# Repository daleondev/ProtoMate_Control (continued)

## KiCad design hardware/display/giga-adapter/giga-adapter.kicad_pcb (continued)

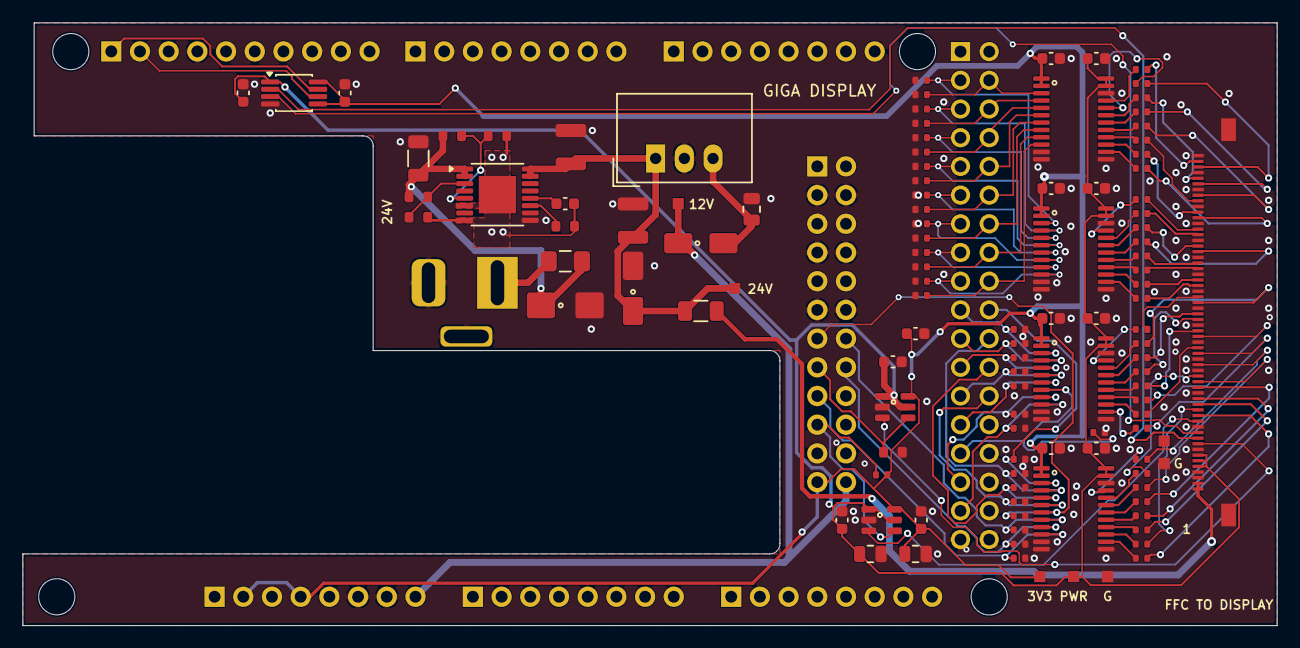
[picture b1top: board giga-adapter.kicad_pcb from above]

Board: 4 copper layers, 111.0 x 53.3 mm, 127 parts (0 on the bottom side), 118 nets.

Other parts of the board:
H1, H2, H3, H4: MountingHole_3.2mm_M3

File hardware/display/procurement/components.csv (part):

Board,Revision,Designators,Installed quantity,Purchase quantity,Circuit value,PCB package,Assembly,Original BOM MPN,Purchase manufacturer,Purchase MPN,Mouser part number,Availability evidence,Indexed stock,Index age,Lookup date,Source URL,Notes
display-adapter,G,J1,1,1,DF23C-50DP-0.5V(92),DF23C-50DP-0.5V,SMT,DF23C-50DP-0.5V(92),Hirose,DF23C-50DP-0.5V(92),798-DF23C50DP05V92,stock-indexed,1575,2 weeks ago,2026-10-22,https://www.mouser.com/en/ProductDetail/Hirose-Connector/DF2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,Exact 50-pin mating plug; fit on display PCB underside.
display-adapter,G,J2,1,1,505110-6091,Molex_505110-6091_1x60_P0.50mm,SMT,505110-6091,Molex,505110-6091,538-505110-6091,stock-indexed,11530,last week,2026-10-22,https://eu.mouser.com/en/ProductDetail/Molex/505110-6091?qs=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,Two bottom-contact sockets per pair; match Molex 15018-0563 Type-A ear-tab cable.
display-adapter,G,U1,1,1,TSR 2-2433 / 3.3V 2A,Converter_DCDC_TRACO_TSR2-xxxx_THT,HAND,TSR 2-2433,TRACO Power,TSR 2-2433,495-TSR2-2433,stock-indexed,6134,3 weeks ago,2026-10-22,https://eu.mouser.com/en/ProductDetail/TRACO-Power/TSR-2-243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,3.3 V / 2 A; through-hole SIP module.
display-adapter,G,"C9, C11",2,2,10u / 50V X7R,C_1210_3225Metric,SMT,GRM32ER71H106KA12L,TAIYO YUDEN,MCJCU32MLB7106KPPDTJ,963-U32MLB7106KPPDTJ,stock-indexed,1535,2 months ago,2026-10-22,https://my.mouser.com/en/ProductDetail/TAIYO-YUDEN/MCJCU32ML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,"Replacement: 10 uF +/-10%, 50 V, X7R, 1210, soft termination; 2.5 +/-0.3 mm height. Original unavailable/region-restricted."
display-adapter,G,C10,1,1,100n / 50V X7R,C_0603_1608Metric,SMT,GRM188R71H104KA93D,KEMET,C0603C104K5RACTU,80-C0603C104K5R,stock-indexed,3941024,last week,2026-10-22,https://cz.mouser.com/en/ProductDetail/KEMET/C0603C104K5RACT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,"Replacement for obsolete original: 100 nF +/-10%, 50 V, X7R, 0603."
display-adapter,G,"C1, C2, C3, C4, C12, C13, C14",7,7,47u / 10V X5R,C_1210_3225Metric,SMT,GRM32ER61A476KE20L,TAIYO YUDEN,MBASL32MSB5476KPNA01,963-BASL32MSB5476KP,stock-indexed,1608,2 weeks ago,2026-10-23,https://lv.mouser.com/en/ProductDetail/TAIYO-YUDEN/MBASL32MS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,"Approved purchasing replacement: 47 uF +/-10%, 10 V, X5R, 1210; 2.5 +/-0.2 mm height. Manufacturer typical DC-bias curve gives approximately 42 uF at 3.3 V and 36 uF at 5 V, not guaranteed minima. Retain supply/ramp/load-step qualification. No footprint change."
display-adapter,G,"C5, C6",2,2,10u / 10V X5R,C_0805_2012Metric,SMT,GRM21BR61A106KE19L,KEMET,C0805C106K8PACTU,80-C0805C106K8P,stock-indexed,235800,last week,2026-10-22,https://eu.mouser.com/en/ProductDetail/KEMET/C0805C106K8PACT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,"Replacement for obsolete original: 10 uF +/-10%, 10 V, X5R, 0805; 1.25 +/-0.15 mm height."
display-adapter,G,"C7, C8, C16, C18, C17",5,5,100n / 50V X7R,C_0603_1608Metric,SMT,GRM188R71C104KA01D,KEMET,C0603C104K5RACTU,80-C0603C104K5R,stock-indexed,3941024,last week,2026-10-22,https://cz.mouser.com/en/ProductDetail/KEMET/C0603C104K5RACT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,"Replacement for EOL original: 100 nF +/-10%, X7R, 0603; voltage rating increased from 16 V to 50 V. Consolidated with display C10."
display-adapter,G,"R2, R3, R4, R5, R8",5,5,47k,R_0402_1005Metric,SMT,RC0402FR-0747KL,YAGEO,RC0402FR-0747KL,603-RC0402FR-0747KL,stock-indexed,986351,last month,2026-10-22,https://eu.mouser.com/en/ProductDetail/YAGEO/RC0402FR-0747KL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,"47 kohm, 1%, 0402."
display-adapter,G,"R6, R7",2,2,4k7,R_0402_1005Metric,SMT,RC0402FR-074K7L,YAGEO,RC0402FR-074K7L,603-RC0402FR-074K7L,stock-indexed,5902658,last week,2026-10-22,https://www.mouser.com/en/ProductDetail/YAGEO/RC0402FR-074K7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,"4.7 kohm, 1%, 0402."
display-adapter,G,U2,1,1,TSR 1-2450 / 5V 1A,Converter_DCDC_TRACO_TSR-1_THT_Trimmed,HAND,TSR 1-2450,TRACO Power,TSR 1-2450,495-TSR-1-2450,stock-indexed,13356,3 weeks ago,2026-10-22,https://eu.mouser.com/en/ProductDetail/TRACO-Power/TSR-1-245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,5 V / 1 A; through-hole SIP module.
display-adapter,G,U3,1,1,TPS7A9101DSKT,WSON-10-1EP_2.5x2.5mm_P0.5mm_EP1.2x2mm,SMT,TPS7A9101DSKR,Texas Instruments,TPS7A9101DSKT,595-TPS7A9101DSKT,stock-indexed,105,3 weeks ago,2026-10-22,https://eu.mouser.com/en/ProductDetail/Texas-Instruments/TPS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,Packaging-only replacement: same DSK-10 chip/pinout; small-reel suffix T instead of R. Exposed pad must be soldered.
display-adapter,G,C15,1,1,47n / 50V X7R,C_0603_1608Metric,SMT,GRM188R71C473KA01D,TDK,C1608X7R1H473K080AA,810-C1608X7R1H473K,stock-indexed,69961,3 weeks ago,2026-10-23,https://www.mouser.com/en/ProductDetail/TDK/C1608X7R1H473K08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,"Approved purchasing replacement: 47 nF +/-10%, 50 V, X7R, 0603; same nominal specification as the unavailable KEMET selection, voltage rating exceeds released BOM 16 V. No footprint change."
display-adapter,G,R9,1,1,31.2k / 0.1%,R_0603_1608Metric,SMT,RT0603BRD0731K2L,Vishay,TNPW060331K2BEEN,71-TNPW060331K2BEEN,stock-indexed,280,last month,2026-10-22,https://www.mouser.tw/en/ProductDetail/Vishay/TNPW060331K2BE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,"Replacement: 31.2 kohm, 0.1%, 25 ppm/K, 0603. Preserve precision LDO ratio; original backordered."
display-adapter,G,R10,1,1,10k / 0.1%,R_0603_1608Metric,SMT,RT0603BRD0710KL,YAGEO,RT0603BRD0710KL,603-RT0603BRD0710KL,stock-indexed,69151,last week,2026-10-22,https://eu.mouser.com/en/ProductDetail/YAGEO/RT0603BRD0710KL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,"10 kohm, 0.1%, 25 ppm/K, 0603. Do not confuse with ordinary 1% 10 kohm."
display-adapter,G,"R11, R12, R13, R14, R15",5,5,10k / 1%,R_0603_1608Metric,SMT,RC0603FR-0710KL,YAGEO,RC0603FR-0710KL,603-RC0603FR-0710KL,stock-indexed,1640807,last week,2026-10-22,https://www.mouser.com/en/ProductDetail/YAGEO/RC0603FR-0710K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,"10 kohm, 1%, 0603."
display-adapter,G,"U4, U6",2,2,TPS3808EG33DBVR,SOT-23-6_UpperPin1,SMT,TPS3808G33DBVR,Texas Instruments,TPS3808EG33DBVR,595-TPS3808EG33DBVR,user-confirmed-orderable,4336,last week,2026-10-23,https://www.mouser.de/ProductDetail/Texas-Instruments/TPS380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,"TPS3808E functional replacement, not a packaging-only substitution: same DBV SOT-23-6 pinout, 3.07 V nominal threshold and active-low open-drain reset. Existing 100 kohm CT pull-ups retain 300 ms nominal delay (180-420 ms). 3.3 V operation is within the 1.7-6 V range; 10 kohm RESET pull-up is compatible. Lower typical quiescent current (0.6 uA). Datasheet undervoltage detect delay is 30 us typical / 50 us maximum at 5% overdrive; retain first-board brownout qualification. User confirmed regional purchase availability for the required two parts on 2026-10-23; stock quantity remains indexed, not live verified. No circuit or footprint change."
display-adapter,G,"R16, R17",2,2,100k,R_0402_1005Metric,SMT,RC0402FR-07100KL,YAGEO,RC0402FR-07100KL,603-RC0402FR-07100KL,stock-indexed,6394487,last month,2026-10-22,https://www.mouser.com/en/ProductDetail/YAGEO/RC0402FR-07100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,"100 kohm, 1%, 0402."
display-adapter,G,U5,1,1,SN74LVC08APW,TSSOP-14_4.4x5mm_P0.65mm,SMT,SN74LVC08APWR,Texas Instruments,SN74LVC08APW,595-SN74LVC08APW,stock-indexed,252,last month,2026-10-22,https://www.mouser.com/en/ProductDetail/Texas-Instruments/SN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,"Packaging-only replacement: same TSSOP-14 PW chip, supplied in tube; original reel variant backordered."
giga-adapter,F,J1,1,1,505110-6091,Molex_505110-6091_1x60_P0.50mm,SMT,505110-6091,Molex,505110-6091,538-505110-6091,stock-indexed,11530,last week,2026-10-22,https://eu.mouser.com/en/ProductDetail/Molex/505110-6091?qs=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,Two bottom-contact sockets per pair; match Molex 15018-0563 Type-A ear-tab cable.
giga-adapter,F,"U1, U2, U3, U4",4,4,SN74AXC8T245PWR,TSSOP-24_4.4x7.8mm_P0.65mm,SMT,SN74AXC8T245PWR,Texas Instruments,SN74AXC8T245PWR,595-SN74AXC8T245PWR,stock-indexed-conflicting,4862,last week,2026-10-22,https://gr.mouser.com/en/c/semiconductors/logic-ics/?mountin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,Latest indexed category page reports stock; older product page reports zero. Confirm four available at basket import. TSSOP-24; no AXCH/LVC substitution.
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
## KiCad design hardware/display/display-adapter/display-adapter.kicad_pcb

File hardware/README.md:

# ProtoMate hardware

Open **[ProtoMate.kicad_pro](ProtoMate.kicad_pro)** in KiCad 10. This is the single
hardware project: the complete system schematic and the linked perfboard layout
share the same project name and component identities.

```text
hardware/
├── ProtoMate.kicad_pro       Project settings and electrical checks
├── ProtoMate.kicad_sch       Root sheet: controller, power, sheet navigation
├── ProtoMate.kicad_pcb       47 × 65 hole perfboard placement and hand wiring
├── sheets/                  Motor interfaces, encoder, storage, headers, switches
├── libraries/               Project-local symbols, footprints and buck 3D model
├── sym-lib-table            Relative symbol-library registration
├── fp-lib-table             Relative footprint-library registration
├── assembly/                Build instructions, parts, hole/wire/harness tables
├── exports/                 Schematic/assembly PDFs and verification reports
└── tools/                   Repeatable checks and export command
```

## Schematic and layout relationship

The root schematic links six child sheets: M1/DM542T, M2/M3/TMC2209,
M1 encoder, storage, perfboard cable headers, and reference limit switches.
Global net names connect these sheets electrically. The connector sheet defines
J101–J107 and J113, and the reference-switch sheet defines J108–J111.
J104 is the ten-way DM542T screw terminal for control, ALM and 24 V power.
The M1 sheet defines pull-up R30; J101 carries ALM to the Nucleo. All connector pin numbers match the layout and
[harness table](assembly/Harness.csv).

All **49 perfboard footprints** have assigned library footprints and native
links to their schematic symbols. These comprise Q1–Q6, R1–R12, R20–R30,
C1–C6, U2/U3, J101–J111 and J113. R10–R12 remain on the layout and are marked DNP.

The **buck U1 and Adafruit A3/A4 modules mount directly at J103/J105/J106**.
These footprints represent their soldered mounting pins and full module
outlines. The module symbols remain excluded from separate PCB placement:
the barrel jack and four-way motor terminals remain on their modules.
J103 has four electrical contacts: 5 V output, output ground, VIN ground and
24 V input. J105/J106 each have ten JP4 control pins plus two JP1 power pins.
J104.9/10 provide the DM542T power connection and the two power-distribution
star joints. Dedicated underside supply/return branches feed each TMC module
through its local C1/C2 bulk capacitor connections. Motor winding cables
connect directly to the drivers. The Nucleo, DM542T, motors, switches and
storage modules remain external. The buck's 63 × 27 mm body follows the supplied
STEP model; its nominal mounting grid is 5.08 mm within each pair and 50.8 mm
between pairs. Its barrel jack receives 24 V at the left edge.

J113 uses eight contacts for six signals and two shared ground returns to the Nucleo: TX (PD5),
RX (PD6), M2 DIAG (PD4), M3 DIAG (PD3), M2 INDEX (PD0) and M3 INDEX (PD1). R29 is the shared UART's 1 kΩ TX
series resistor. J105/J106 pin 9 is UART, pin 7 is DIAG and pin 8 is INDEX.
Address straps are M2 MS1/MS2 = GND/GND and M3 = 3.3 V/GND. Both SPRD jumpers
stay open. Firmware configures current and 16 microsteps before enable; the
potentiometers do not set current in UART mode. See the
[UART wiring and firmware settings](../README.md#tmc2209-uart-configuration-and-diagnostics).

The `.kicad_pcb` is a map for a purchased individual-pad board: F.Cu represents
top jumpers, B.Cu represents solder-side wires, and vias represent wire passages.
Use the **65 × 47-hole board**, oriented as **47 columns × 65 rows**, A1–BM47,
at 2.54 mm pitch. The outer hole centres span **116.84 × 162.56 mm**; the
nominal outline is 119.38 × 165.10 mm with half-pitch margins. J104 and both TMC modules
sit along the top edge with their cable entries facing outward. J107 sits below
J104, keeping both motor-1 cables together. J101, J113, J102 and J108 form a
left-edge Nucleo connector bank with 9.1 mm gaps between bodies and pin 1 at
the bottom of every header. The encoder receiver and level converters occupy
the centre-left; the DM542T transistor stages occupy the right interior.
The buck sits at the bottom left, with the three switch cable headers at the
bottom right. Q1–Q3 have 30.48 mm between stages; Q4–Q6 have
15.24 mm between stages. Decoupling capacitors stay close to their ICs.
The barrel jack faces the left edge.
The wire schedule specifies underside routes and insulated top crossovers
through dedicated free holes. All wire ends are soldered underneath. J101's pin 1 is
at Z4; odd pins run up column 4 and even pins up column 3. The 11 designated
power connections all stay underneath and use 0.5 mm² insulated copper wire;
wire drawing width does not specify conductor size.
Use the [assembly instructions](assembly/README.md) to build it.

The STEP engine uses one 32-bit TIM2 with DMA: M1 = PA0/CN10.29,
M2 = PB10/CN10.32, M3 = PB11/CN10.34 (channels 1/3/4, all AF1).
DIR uses PE12/CN10.26, PE13/CN10.10, PE14/CN10.8; the shared active-low
enable is PE15/CN10.30. These signals use J101 pins 1/3/5/7/9/11/12. J101.4 carries M1 ALM,
J101.8 supplies 3.3 V, and pins 2/6/10 are STEP ground returns.
The harness table, Nucleo symbol and layout notes specify the cable destinations.
Keep PA0's SB75 ON and the user
button on PC13. TIM5 is the runtime clock; TIM7 provides an internal finite-move
completion check and uses no connector pin. PE9/PE11 (TIM1) and PC6/PC7
(TIM8) are reserved for possible additional encoders, with no cables fitted.

Set the onboard **STLINK-V3 MCO to HSE/5 (5 MHz)**. CubeMX uses that external
clock in bypass mode for a 480 MHz CPU, 240 MHz timer kernels and 10 MHz STEP
counter. This persistent ST-Link setting is configured separately from CubeMX;
follow the [clock setup procedure](../docs/stepper-hardware-test.md#clock-source-configuration)
when preparing a board.

The three reference-switch cables connect to J109 (M1), J110 (M2), and J111
(M3), each with pin 1 = REF and pin 2 = GND. J108 returns the signals to
PE7/CN10.20, PE8/CN10.18 and PE10/CN10.24 on pins 1/2/3; pin 4
connects their shared return to Nucleo GND/CN10.22. This is passive wiring using the
firmware's internal 3.3 V pull-ups. SW1–SW3 are shown released with COM–NC
closed: low when released, high when pressed or unplugged. Their schematic
contact names are functional identities, not an asserted Creality connector
pin order; verify the normally closed pair by continuity before making cables.

J104.7/8 connects DM542T ALM+/ALM−; J101.4 returns the signal
to PF2/CN9.17, sharing the motion harness ground. R30 pulls ALM+ to 3.3 V through 4.7 kΩ.
The default normally conducting alarm reads low when healthy and high on a
fault or open cable. See the
[alarm wiring and recovery behavior](../README.md#dm542t-alarm-input).

## Controller harness

Use four short harnesses between the Nucleo and perfboard: J101 (12 contacts),
J102 (6), J108 (4), and J113 (8). Each signal appears exactly once; 3.3 V
enters only at J101.8. J101 also carries the M1 alarm signal.

The nine ground conductors have deliberate roles: three STEP returns at J101,
three encoder returns at J102, one shared switch return at J108, and two shared
UART/diagnostic returns at J113. Twist each STEP and encoder signal with its
assigned ground. Bundle the slower signals with their shared returns; keep these
short local harnesses separate from motor and 24 V cables. The ground conductors
may join at a ground bus beside the Nucleo; they do not need separate Nucleo GND
pins. Use a short, solid connection from that bus to Nucleo GND.

Module ground contacts and address straps remain connected as required by the
modules. Motor supply current uses the dedicated power branches. Ground links
in the perfboard wire schedule are required even where cable returns are shared.

## Editing workflow

1. Open the project above, then its schematic and PCB editors. Edit electrical
   connections and component assignments in the schematic.
2. Save the schematic and use **Tools → Update PCB from Schematic (F8)**.
   Keep UUID-based association; leave **Re-link footprints to schematic symbols
   based on their reference designators** unchecked. Review the proposed changes.
3. Apply the update, then place new parts and adjust the hand-wire routes in the
   PCB editor. Use the 2.54 mm hole grid for leads and wire passages. F8 transfers
   connectivity and component changes; it does not design the new wiring routes.
4. Maintain [Wires.csv](assembly/Wires.csv) after routing changes and
   [Harness.csv](assembly/Harness.csv) after cable/connector changes. Review
   mounting details in [Parts.csv](assembly/Parts.csv). Run the refresh command
   below before using or sharing the assembly documents.

Project-local footprints preserve the actual grid spacing and Diotec E/B/C
pad identities. They resolve through `${KIPRJMOD}`, so moving or cloning the
repository does not require personal library paths. The X/Y axial resistor
patterns describe the two existing orientations of the assembly drawing.

There is no separate netlist-import step or second electrical design to maintain.
KiCad's schematic-to-board check verifies the association, footprint identity,
value, and pad connectivity in the saved project.

## Checks and exports

From the repository root:

```sh
python3 hardware/tools/refresh.py
```

Requires KiCad 10 (`kicad-cli` and its `pcbnew` Python module), Python 3 and
Poppler's `pdfunite`. The command checks ERC, DRC **with schematic parity**,
symbol links, pad nets, the hole grid, wire endpoints/connectivity, module body
clearance, mounting contacts, dedicated power branches and harness destinations.
All 33 motor, encoder, reference, ALM/UART/DIAG and storage signal contacts
are checked against CubeMX, along with reference pull-ups/edges, encoder index
polarity, DIAG pulls/edges, UART settings/address straps and the disabled startup level. It updates:

- [Wiring.pdf](exports/Wiring.pdf): complete seven-sheet system schematic.
- [Assembly.pdf](exports/Assembly.pdf): placement, top wires, mirrored underside
  and combined overview, at actual size.
- [Holes.csv](assembly/Holes.csv) and [System_Parts.csv](assembly/System_Parts.csv):
  generated pin locations and system components, including board/external scope.
- [ERC.rpt](exports/ERC.rpt), [DRC.rpt](exports/DRC.rpt) and
  [Verification.txt](exports/Verification.txt): checks of the saved native files.

Use `python3 hardware/tools/refresh.py --check-only` to refresh just the checks.
The tool reads the native design; it never regenerates or overwrites its
schematic or layout. Wire lengths and side choices in the assembly schedule
remain manually reviewed when routing changes. The checks validate a wiring
model, not solder joints or measured encoder-interface timing.

Manufacturing silkscreen and missing-courtyard checks are waived for this
hand-wiring map. Electrical clearance, unconnected pads, schematic parity and
local footprint-library consistency are checked. No fabrication outputs are
generated.

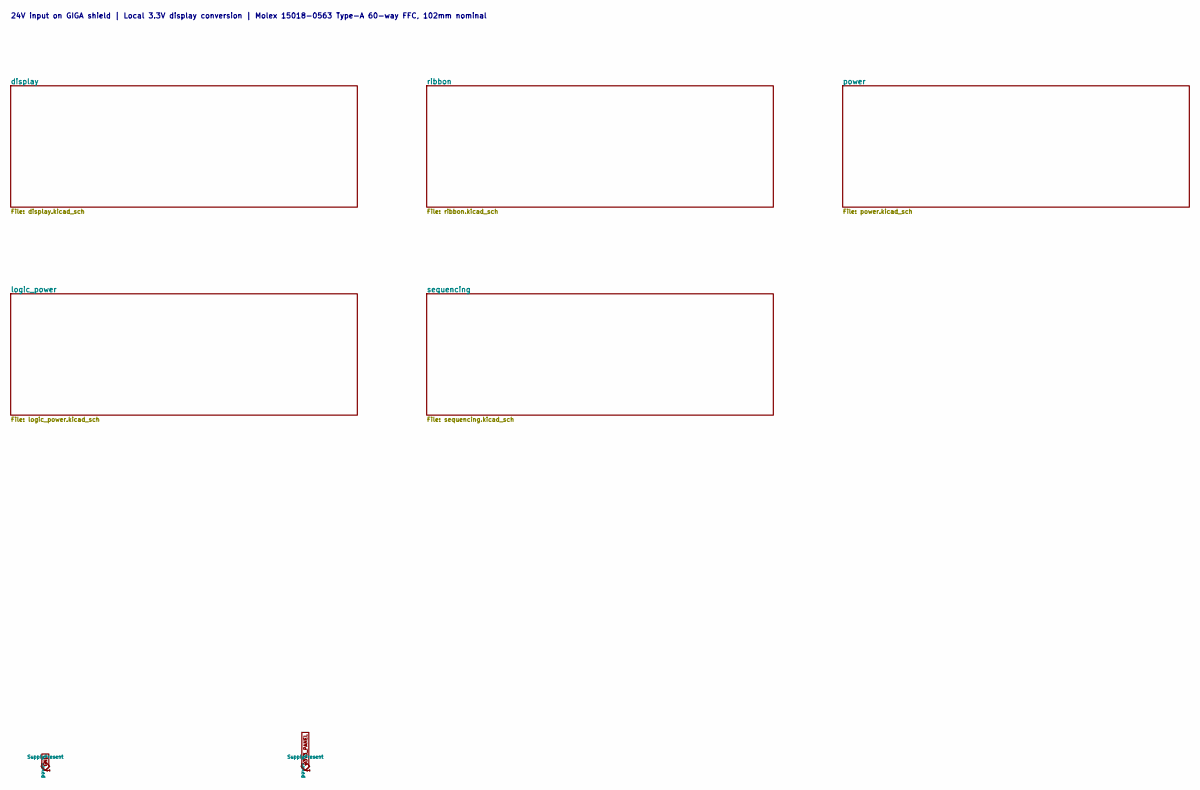
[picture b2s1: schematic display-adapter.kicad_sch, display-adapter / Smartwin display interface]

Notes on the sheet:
24V input on GIGA shield | Local 3.3V display conversion | Molex 15018-0563 Type-A 60-way FFC, 102mm nominal

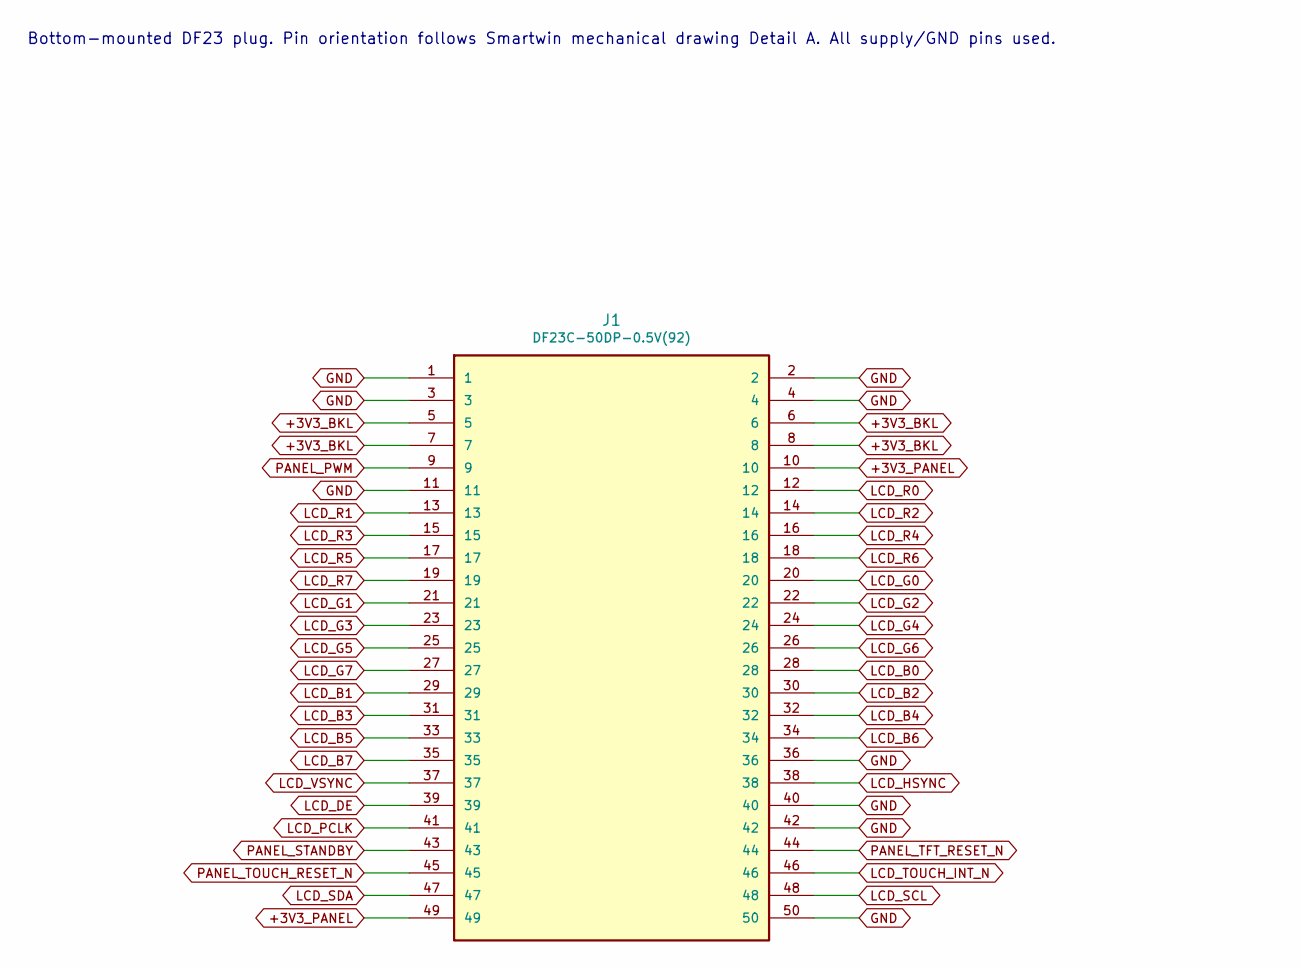
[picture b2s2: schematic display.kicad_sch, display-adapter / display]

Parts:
J1: DF23C-50DP-0.5V(92); DF23C-50DP-0.5V; MPN DF23C-50DP-0.5V(92)

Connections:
+3V3_BKL: J1.5, J1.6, J1.7, J1.8; also elsewhere on the board
+3V3_PANEL: J1.10, J1.49; also elsewhere on the board
GND: J1.1, J1.2, J1.3, J1.4, J1.11, J1.36, J1.40, J1.42, J1.50; also elsewhere on the board
LCD_B0: J1.28; also elsewhere on the board
LCD_B1: J1.29; also elsewhere on the board
LCD_B2: J1.30; also elsewhere on the board
LCD_B3: J1.31; also elsewhere on the board
LCD_B4: J1.32; also elsewhere on the board
LCD_B5: J1.33; also elsewhere on the board
LCD_B6: J1.34; also elsewhere on the board
LCD_B7: J1.35; also elsewhere on the board
LCD_DE: J1.39; also elsewhere on the board
LCD_G0: J1.20; also elsewhere on the board
LCD_G1: J1.21; also elsewhere on the board
LCD_G2: J1.22; also elsewhere on the board
LCD_G3: J1.23; also elsewhere on the board
LCD_G4: J1.24; also elsewhere on the board
LCD_G5: J1.25; also elsewhere on the board
LCD_G6: J1.26; also elsewhere on the board
LCD_G7: J1.27; also elsewhere on the board
LCD_HSYNC: J1.38; also elsewhere on the board
LCD_PCLK: J1.41; also elsewhere on the board
LCD_R0: J1.12; also elsewhere on the board
LCD_R1: J1.13; also elsewhere on the board
LCD_R2: J1.14; also elsewhere on the board
LCD_R3: J1.15; also elsewhere on the board
LCD_R4: J1.16; also elsewhere on the board
LCD_R5: J1.17; also elsewhere on the board
LCD_R6: J1.18; also elsewhere on the board
LCD_R7: J1.19; also elsewhere on the board
LCD_SCL: J1.48; also elsewhere on the board
LCD_SDA: J1.47; also elsewhere on the board
LCD_TOUCH_INT_N: J1.46; also elsewhere on the board
LCD_VSYNC: J1.37; also elsewhere on the board
PANEL_PWM: J1.9; also elsewhere on the board
PANEL_STANDBY: J1.43; also elsewhere on the board
PANEL_TFT_RESET_N: J1.44; also elsewhere on the board
PANEL_TOUCH_RESET_N: J1.45; also elsewhere on the board

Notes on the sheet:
Bottom-mounted DF23 plug. Pin orientation follows Smartwin mechanical drawing Detail A. All supply/GND pins used.

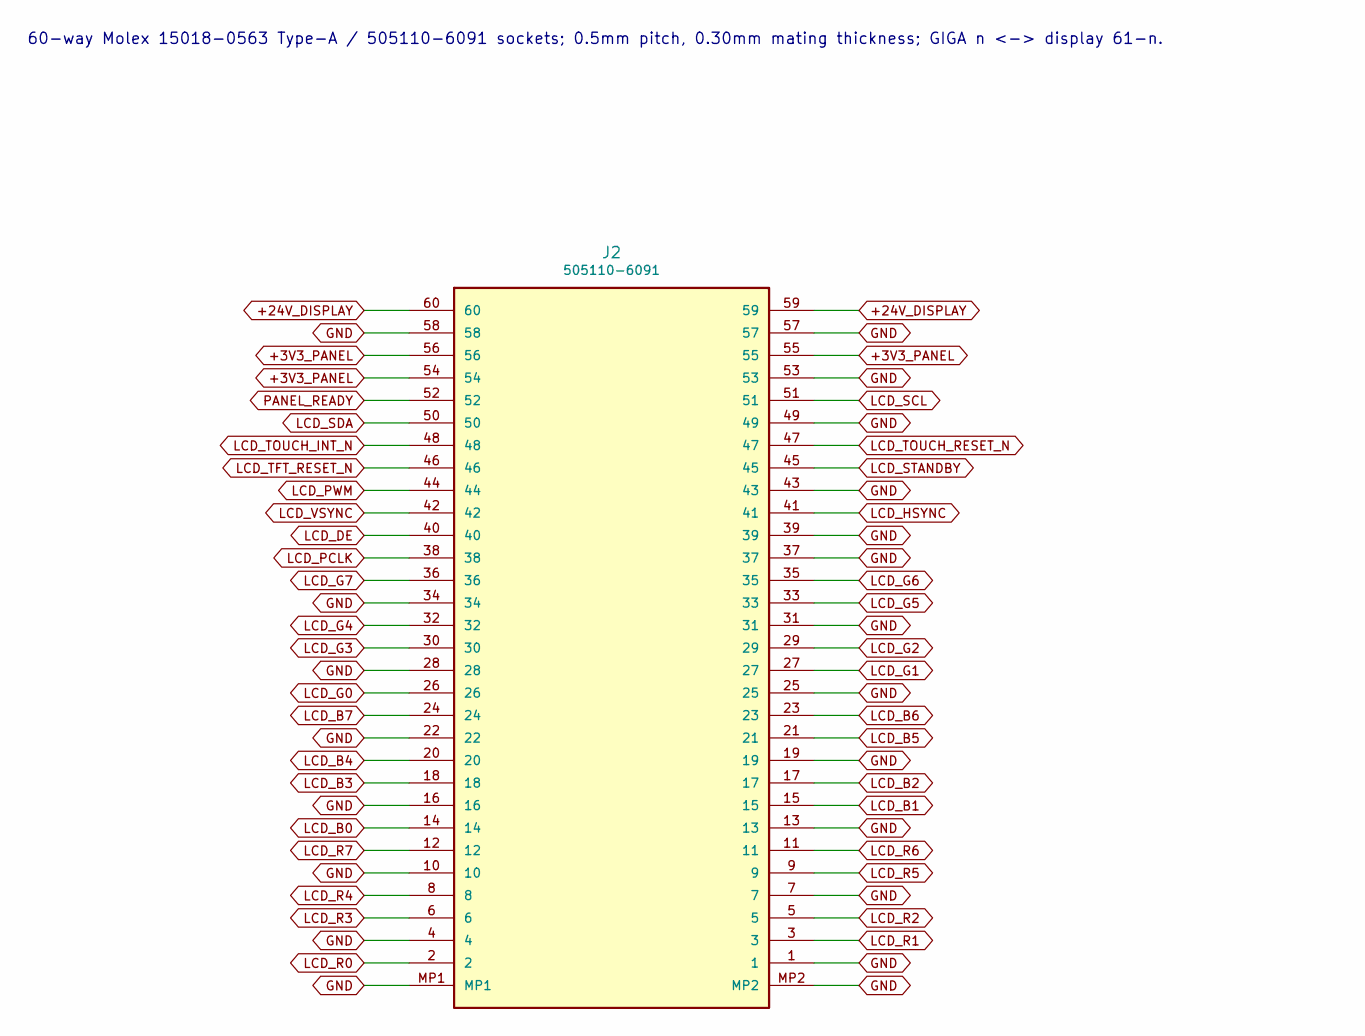
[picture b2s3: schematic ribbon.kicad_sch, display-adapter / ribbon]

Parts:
J2: 505110-6091; Molex_505110-6091_1x60_P0.50mm; MPN 505110-6091

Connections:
+3V3_PANEL: J2.54, J2.55, J2.56; also elsewhere on the board
+24V_DISPLAY: J2.59, J2.60; also elsewhere on the board
GND: J2.1, J2.4, J2.7, J2.10, J2.13, J2.16, J2.19, J2.22, J2.25, J2.28, J2.31, J2.34, J2.37, J2.39, J2.43, J2.49, J2.53, J2.57, J2.58, J2.MP1, J2.MP2; also elsewhere on the board
LCD_B0: J2.14; also elsewhere on the board
LCD_B1: J2.15; also elsewhere on the board
LCD_B2: J2.17; also elsewhere on the board
LCD_B3: J2.18; also elsewhere on the board
LCD_B4: J2.20; also elsewhere on the board
LCD_B5: J2.21; also elsewhere on the board
LCD_B6: J2.23; also elsewhere on the board
LCD_B7: J2.24; also elsewhere on the board
LCD_DE: J2.40; also elsewhere on the board
LCD_G0: J2.26; also elsewhere on the board
LCD_G1: J2.27; also elsewhere on the board
LCD_G2: J2.29; also elsewhere on the board
LCD_G3: J2.30; also elsewhere on the board
LCD_G4: J2.32; also elsewhere on the board
LCD_G5: J2.33; also elsewhere on the board
LCD_G6: J2.35; also elsewhere on the board
LCD_G7: J2.36; also elsewhere on the board
LCD_HSYNC: J2.41; also elsewhere on the board
LCD_PCLK: J2.38; also elsewhere on the board
LCD_PWM: J2.44; also elsewhere on the board
LCD_R0: J2.2; also elsewhere on the board
LCD_R1: J2.3; also elsewhere on the board
LCD_R2: J2.5; also elsewhere on the board
LCD_R3: J2.6; also elsewhere on the board
LCD_R4: J2.8; also elsewhere on the board
LCD_R5: J2.9; also elsewhere on the board
LCD_R6: J2.11; also elsewhere on the board
LCD_R7: J2.12; also elsewhere on the board
LCD_SCL: J2.51; also elsewhere on the board
LCD_SDA: J2.50; also elsewhere on the board
LCD_STANDBY: J2.45; also elsewhere on the board
LCD_TFT_RESET_N: J2.46; also elsewhere on the board
LCD_TOUCH_INT_N: J2.48; also elsewhere on the board
LCD_TOUCH_RESET_N: J2.47; also elsewhere on the board
LCD_VSYNC: J2.42; also elsewhere on the board
PANEL_READY: J2.52; also elsewhere on the board

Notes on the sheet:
60-way Molex 15018-0563 Type-A / 505110-6091 sockets; 0.5mm pitch, 0.30mm mating thickness; GIGA n <-> display 61-n.

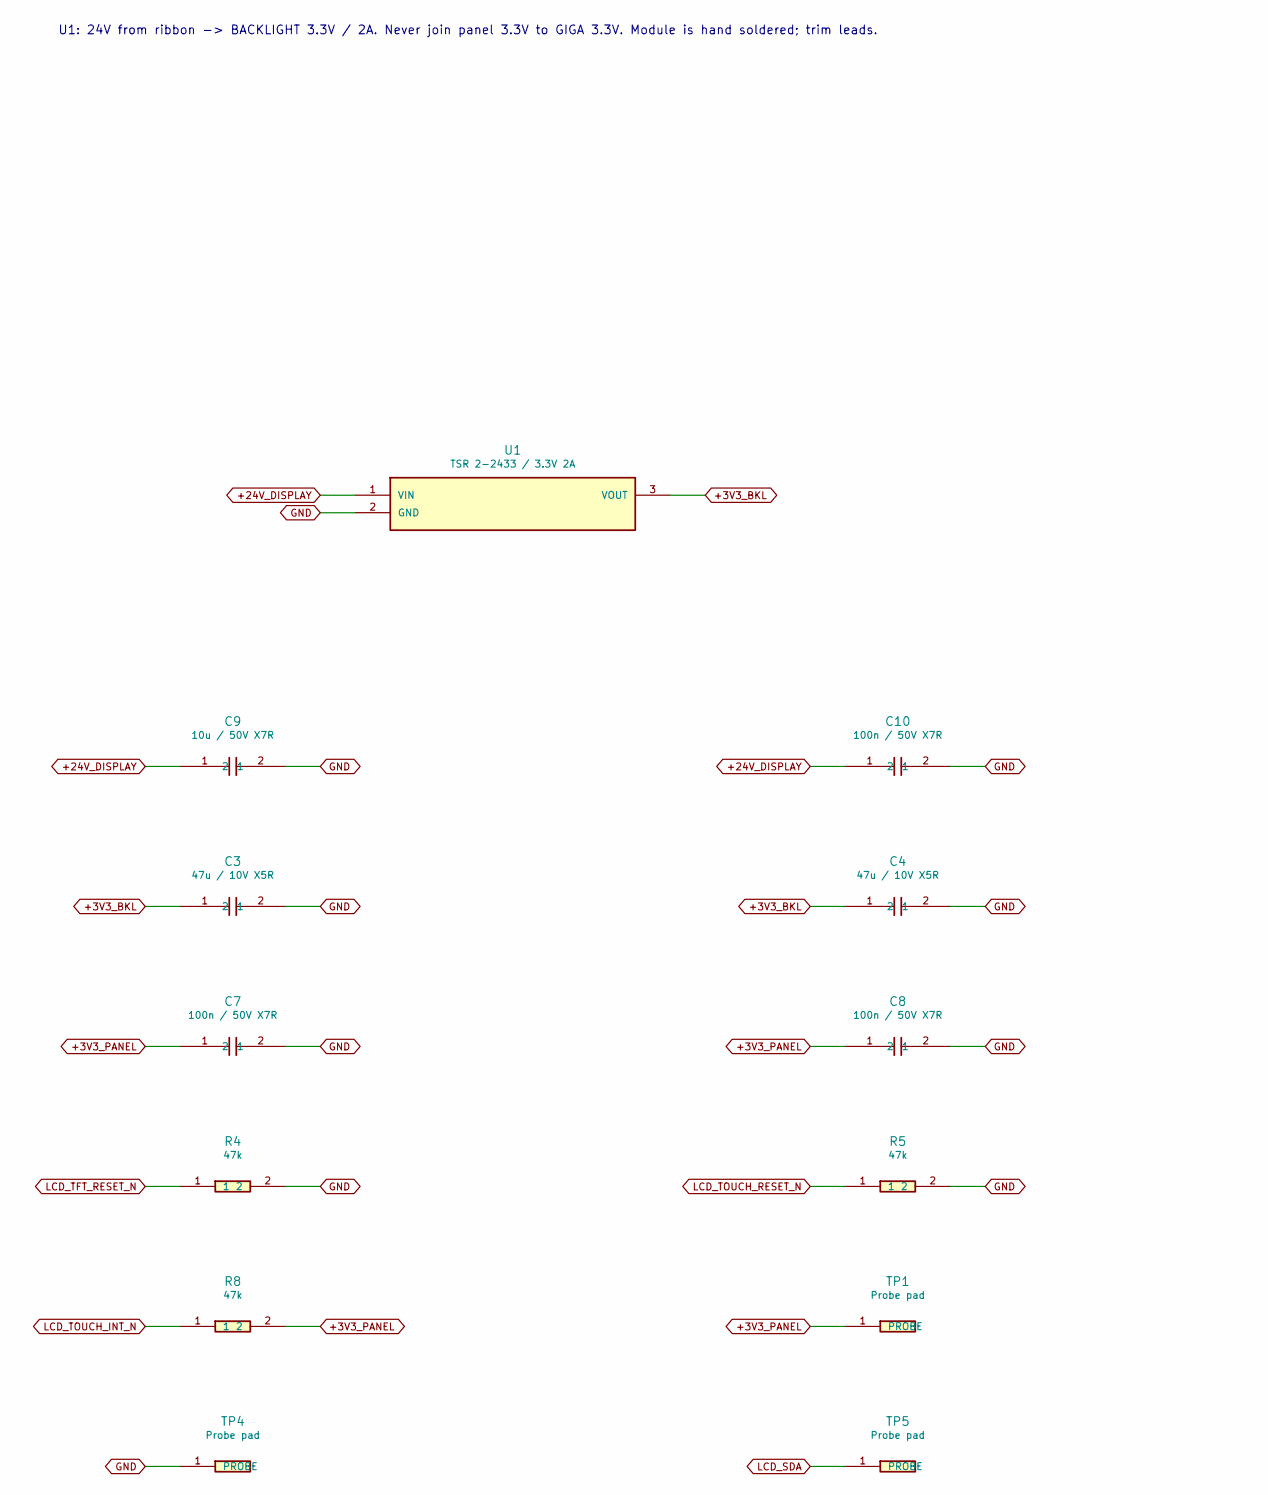
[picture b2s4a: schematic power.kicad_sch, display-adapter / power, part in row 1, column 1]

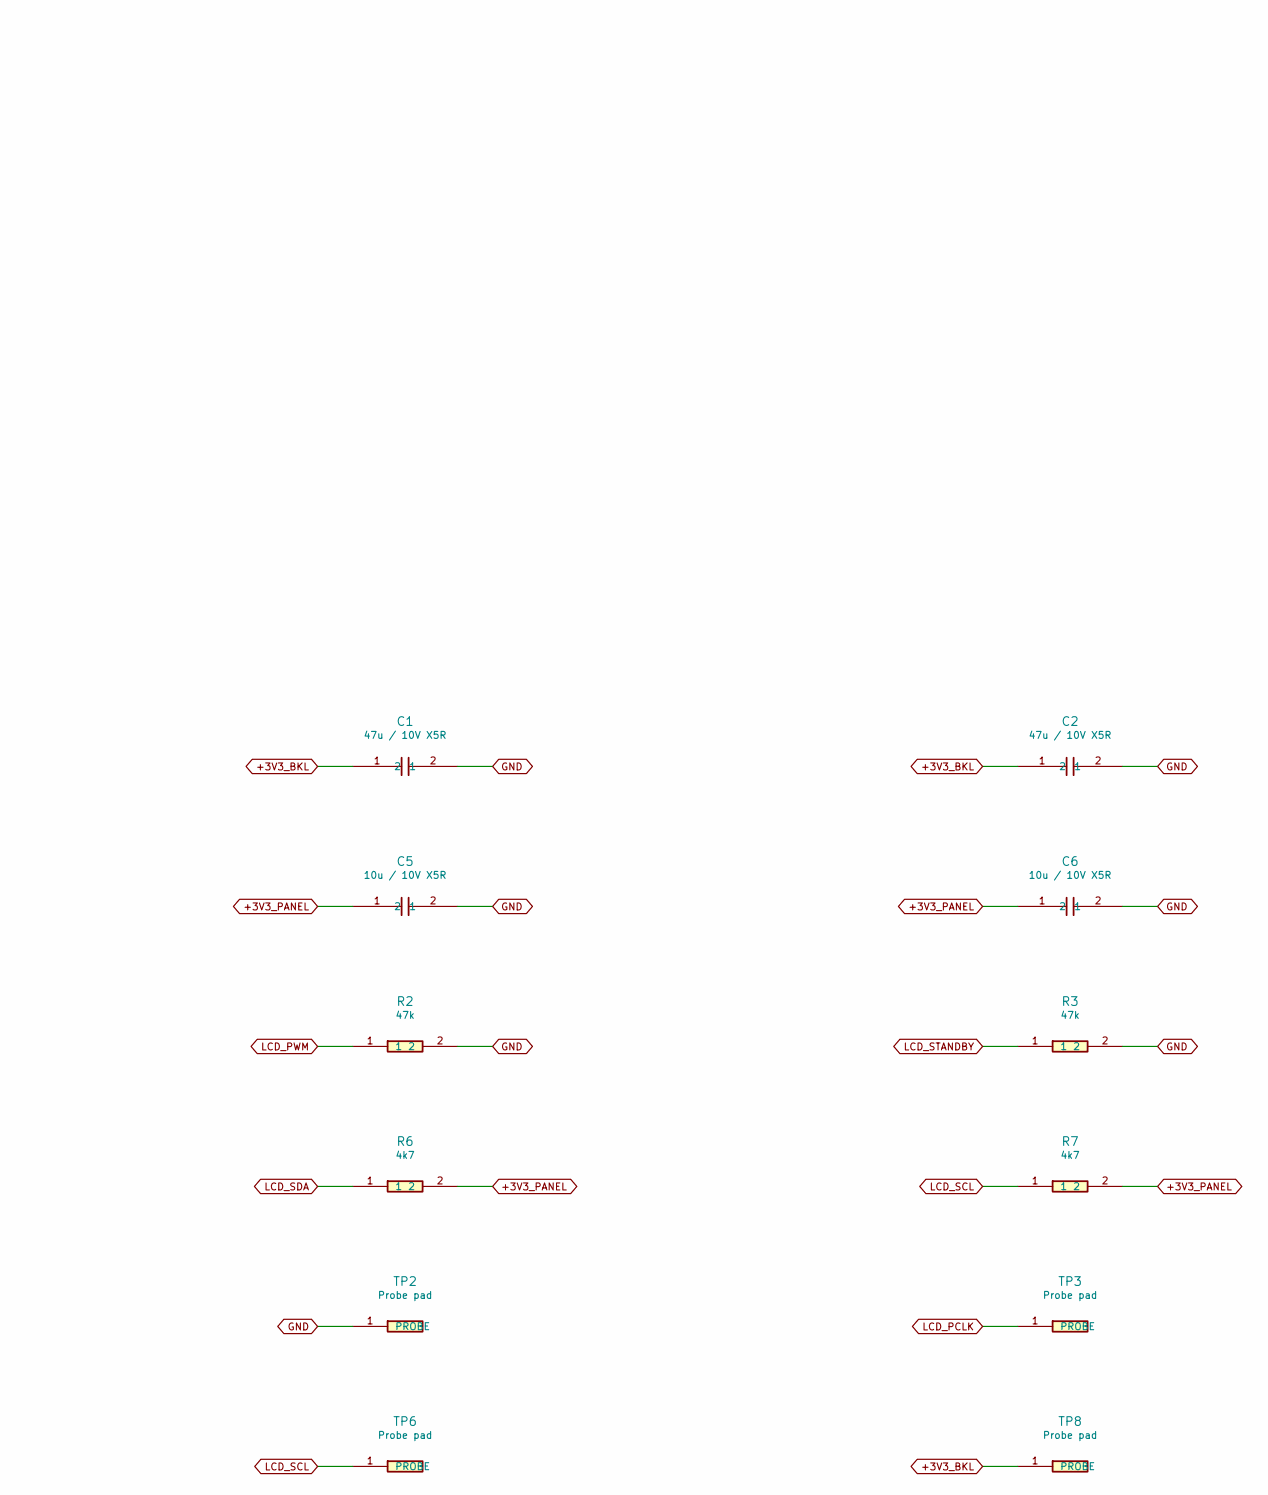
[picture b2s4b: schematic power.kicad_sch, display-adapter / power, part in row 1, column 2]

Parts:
C1, C2, C3, C4: 47u / 10V X5R; C_1210_3225Metric; MPN MBASL32MSB5476KPNA01
C5, C6: 10u / 10V X5R; C_0805_2012Metric; MPN C0805C106K8PACTU
C7, C8, C10: 100n / 50V X7R; C_0603_1608Metric; MPN C0603C104K5RACTU
C9: 10u / 50V X7R; C_1210_3225Metric; MPN MCJCU32MLB7106KPPDTJ
R2, R3, R4, R5, R8: 47k; R_0402_1005Metric; MPN RC0402FR-0747KL
R6, R7: 4k7; R_0402_1005Metric; MPN RC0402FR-074K7L
TP1, TP2, TP3, TP4, TP5, TP6, TP8: Probe pad; TestPoint_1.0mm; MPN PCB copper feature
U1: TSR 2-2433 / 3.3V 2A; Converter_DCDC_TRACO_TSR2-xxxx_THT; MPN TSR 2-2433

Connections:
+3V3_BKL: C1.1, C2.1, C3.1, C4.1, TP8.1, U1.3 (VOUT); also elsewhere on the board
+3V3_PANEL: C5.1, C6.1, C7.1, C8.1, R6.2, R7.2, R8.2, TP1.1; also elsewhere on the board
+24V_DISPLAY: C9.1, C10.1, U1.1 (VIN); also elsewhere on the board
GND: C1.2, C2.2, C3.2, C4.2, C5.2, C6.2, C7.2, C8.2, C9.2, C10.2, R2.2, R3.2, R4.2, R5.2, TP2.1, TP4.1, U1.2 (GND); also elsewhere on the board
LCD_PCLK: TP3.1; also elsewhere on the board
LCD_PWM: R2.1; also elsewhere on the board
LCD_SCL: R7.1, TP6.1; also elsewhere on the board
LCD_SDA: R6.1, TP5.1; also elsewhere on the board
LCD_STANDBY: R3.1; also elsewhere on the board
LCD_TFT_RESET_N: R4.1; also elsewhere on the board
LCD_TOUCH_INT_N: R8.1; also elsewhere on the board
LCD_TOUCH_RESET_N: R5.1; also elsewhere on the board

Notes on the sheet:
U1: 24V from ribbon -> BACKLIGHT 3.3V / 2A. Never join panel 3.3V to GIGA 3.3V. Module is hand soldered; trim leads.

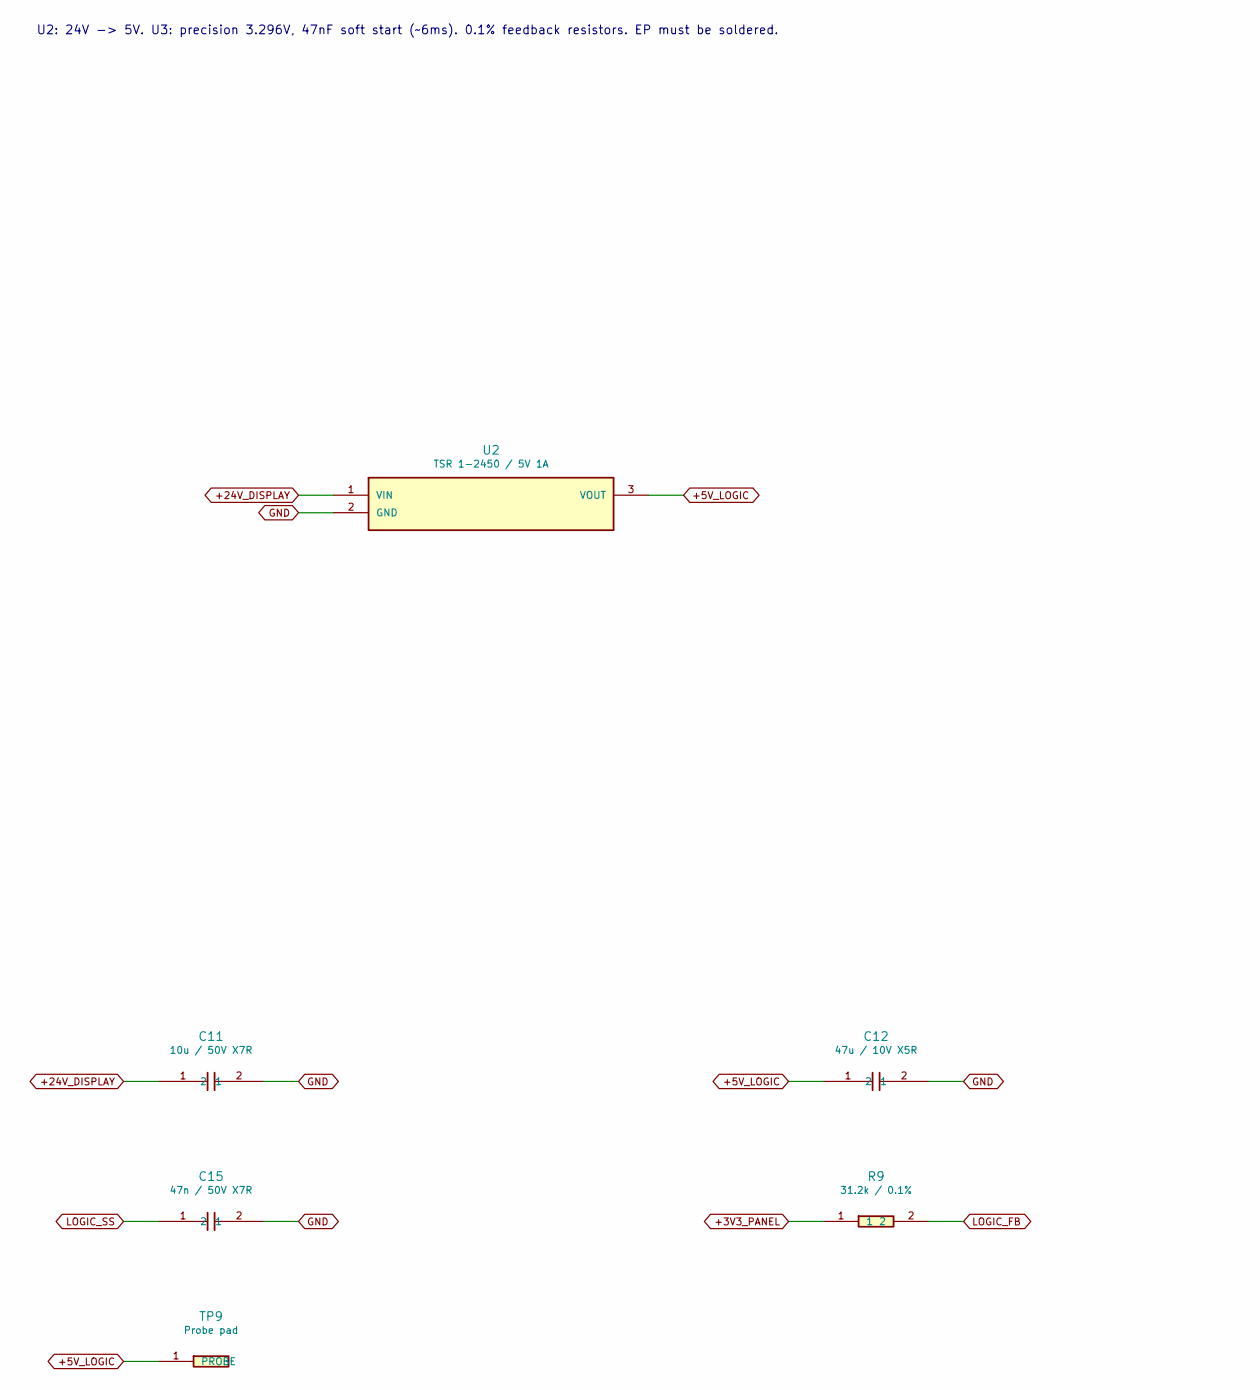
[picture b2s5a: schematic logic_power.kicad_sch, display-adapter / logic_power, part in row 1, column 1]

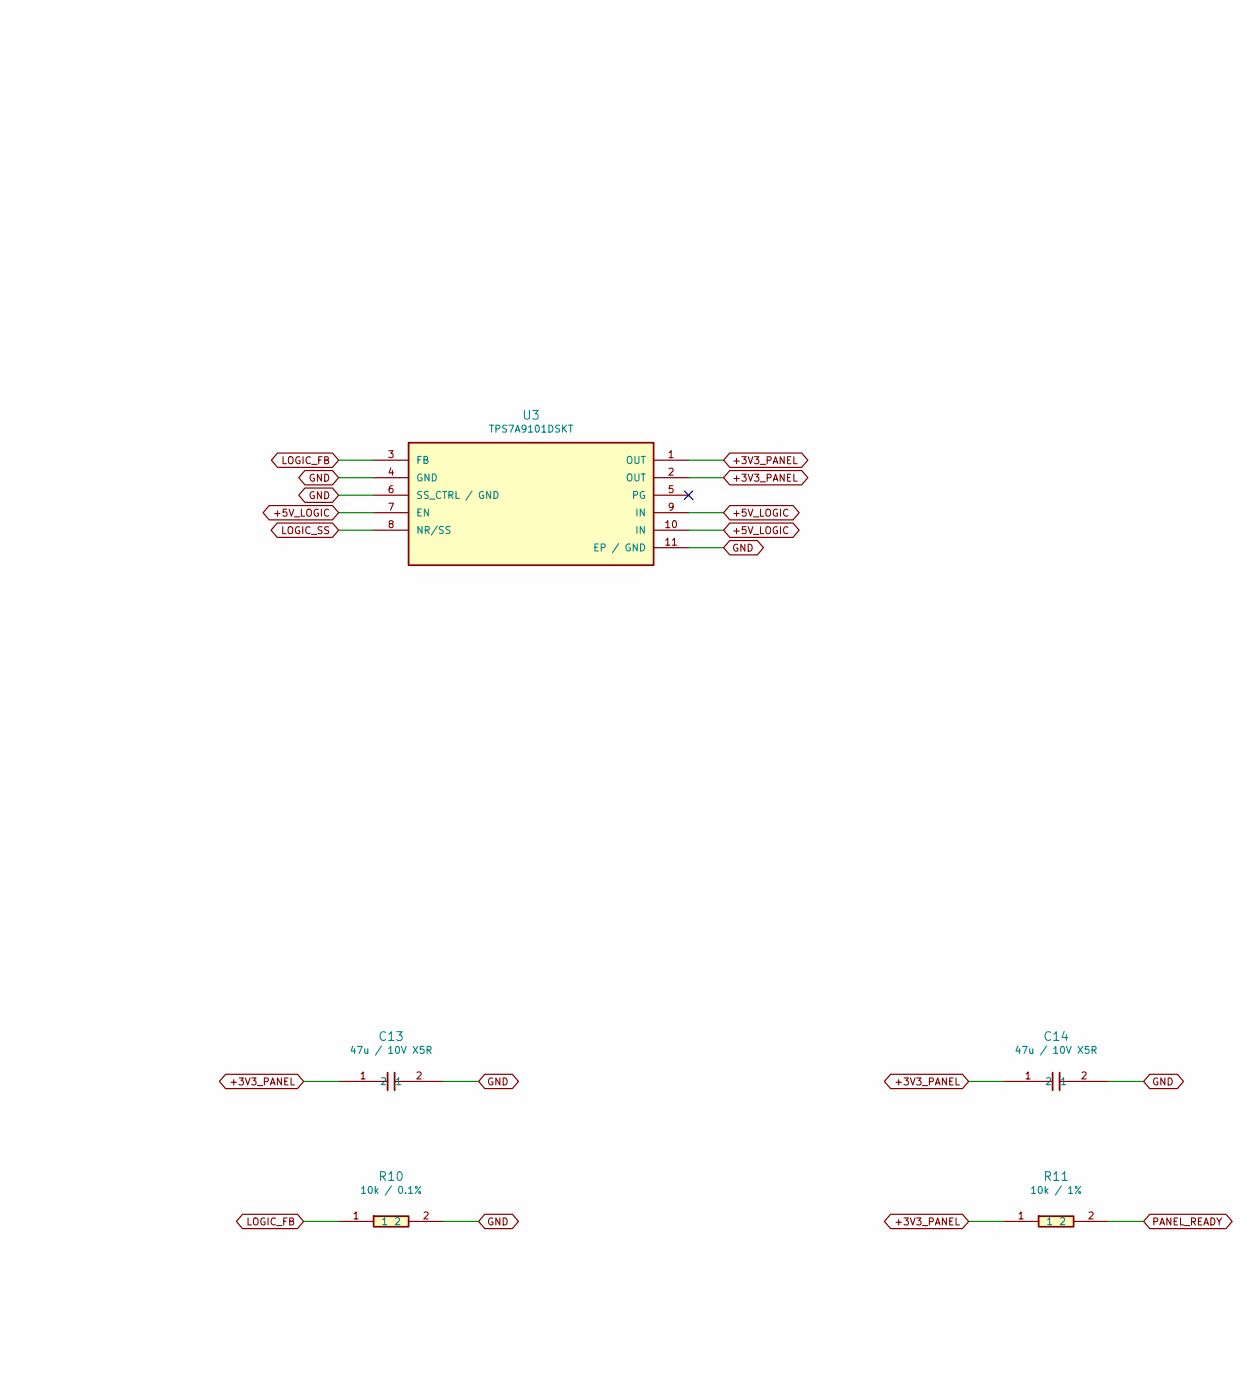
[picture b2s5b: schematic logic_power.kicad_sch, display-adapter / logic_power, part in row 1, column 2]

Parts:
C11: 10u / 50V X7R; C_1210_3225Metric; MPN MCJCU32MLB7106KPPDTJ
C12, C13, C14: 47u / 10V X5R; C_1210_3225Metric; MPN MBASL32MSB5476KPNA01
C15: 47n / 50V X7R; C_0603_1608Metric; MPN C1608X7R1H473K080AA
R9: 31.2k / 0.1%; R_0603_1608Metric; MPN TNPW060331K2BEEN
R10: 10k / 0.1%; R_0603_1608Metric; MPN RT0603BRD0710KL
R11: 10k / 1%; R_0603_1608Metric; MPN RC0603FR-0710KL
TP9: Probe pad; TestPoint_1.0mm; MPN PCB copper feature
U2: TSR 1-2450 / 5V 1A; Converter_DCDC_TRACO_TSR-1_THT_Trimmed; MPN TSR 1-2450
U3: TPS7A9101DSKT; WSON-10-1EP_2.5x2.5mm_P0.5mm_EP1.2x2mm; MPN TPS7A9101DSKT

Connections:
+3V3_PANEL: C13.1, C14.1, R9.1, R11.1, U3.1 (OUT), U3.2 (OUT); also elsewhere on the board
+5V_LOGIC: C12.1, TP9.1, U2.3 (VOUT), U3.7 (EN), U3.9 (IN), U3.10 (IN)
+24V_DISPLAY: C11.1, U2.1 (VIN); also elsewhere on the board
GND: C11.2, C12.2, C13.2, C14.2, C15.2, R10.2, U2.2 (GND), U3.4 (GND), U3.6 (SS_CTRL / GND), U3.11 (EP / GND); also elsewhere on the board
LOGIC_FB: R9.2, R10.1, U3.3 (FB)
LOGIC_SS: C15.1, U3.8 (NR/SS)
PANEL_READY: R11.2; also elsewhere on the board

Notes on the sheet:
U2: 24V -> 5V. U3: precision 3.296V, 47nF soft start (~6ms). 0.1% feedback resistors. EP must be soldered.
